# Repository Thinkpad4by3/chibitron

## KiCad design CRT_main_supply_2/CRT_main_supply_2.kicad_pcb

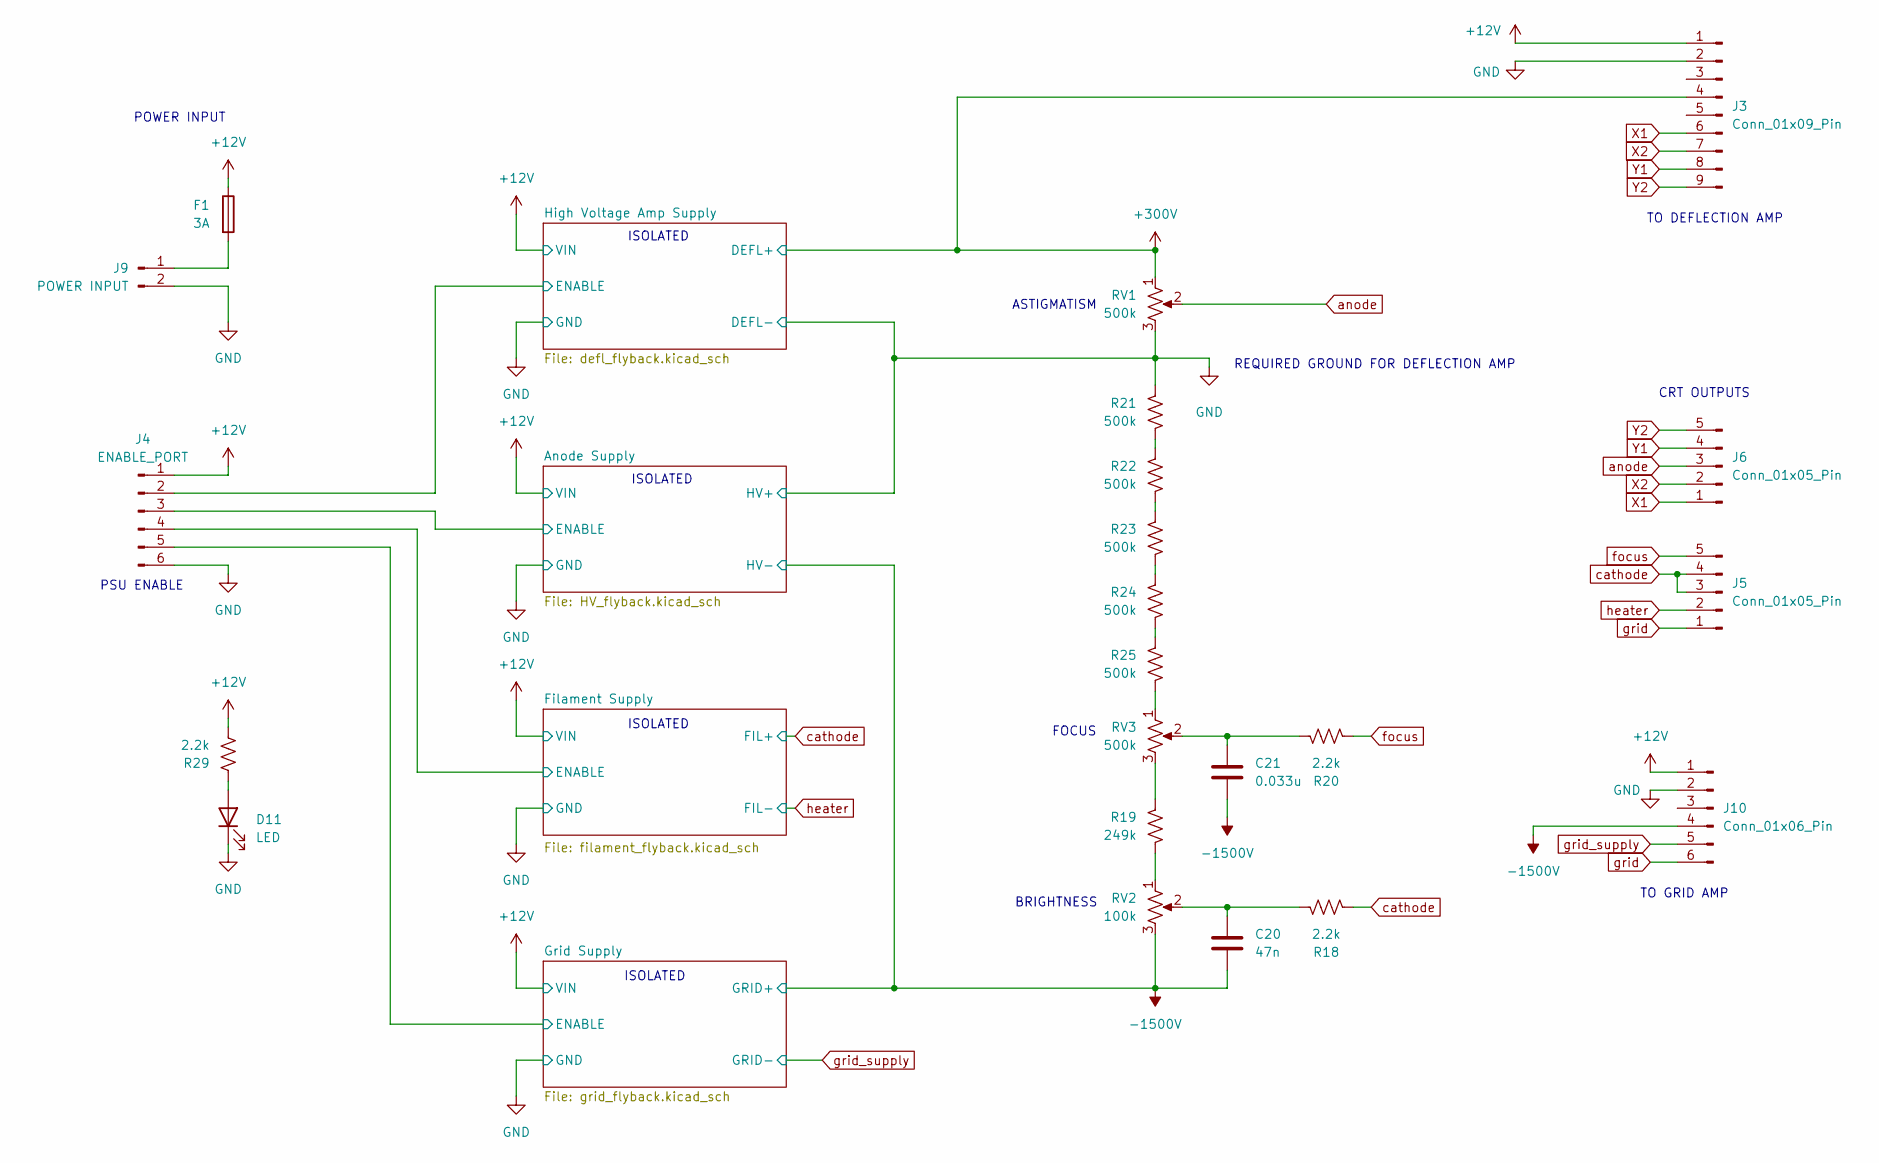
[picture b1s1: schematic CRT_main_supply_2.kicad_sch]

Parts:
C20: 47n; C_0805_2012Metric
C21: 0.033u; C_2225_5664Metric
D11: LED; LED_0805_2012Metric
F1: 3A; Fuse_1206_3216Metric
J3: Conn_01x09_Pin; Molex_KK-396_5273-09A_1x09_P3.96mm_Vertical
J4: ENABLE_PORT; Molex_KK-396_5273-06A_1x06_P3.96mm_Vertical
J5, J6: Conn_01x05_Pin; Molex_KK-396_5273-05A_1x05_P3.96mm_Vertical
J9: POWER INPUT; Molex_KK-396_5273-02A_1x02_P3.96mm_Vertical
J10: Conn_01x06_Pin; Molex_KK-396_5273-06A_1x06_P3.96mm_Vertical
R18, R20, R29: 2.2k; R_0805_2012Metric
R19: 249k; R_1206_3216Metric
R21, R22, R23, R24, R25: 500k; R_1206_3216Metric
RV1, RV3: 500k; Potentiometer_Bourns_3296W_Vertical
RV2: 100k; Potentiometer_Bourns_3296W_Vertical

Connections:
+12V: F1.1, J3.1, J4.1, J10.1, R29.2; also elsewhere on the board
+300V: J3.4, RV1.1; also elsewhere on the board
-1500V: C20.2, C21.2, J10.4, RV2.3; also elsewhere on the board
/Anode Supply/ENABLE: J4.3; also elsewhere on the board
/Filament Supply/ENABLE: J4.4; also elsewhere on the board
/Grid Supply/ENABLE: J4.5; also elsewhere on the board
/High Voltage Amp Supply/ENABLE: J4.2; also elsewhere on the board
GND: D11.1 (K), J3.2, J4.6, J9.2, J10.2, R21.1, RV1.3; also elsewhere on the board
unnamed: C20.1, R18.1, RV2.2
unnamed: C21.1, R20.1, RV3.2
unnamed: D11.2 (A), R29.1
unnamed: F1.2, J9.1
unnamed: R19.1, RV3.3
unnamed: R19.2, RV2.1
unnamed: R21.2, R22.1
unnamed: R22.2, R23.1
unnamed: R23.2, R24.1
unnamed: R24.2, R25.1
unnamed: R25.2, RV3.1
X1: J3.6, J6.1
X2: J3.7, J6.2
Y1: J3.8, J6.4
Y2: J3.9, J6.5
anode: J6.3, RV1.2
cathode: J5.3, J5.4, R18.2; also elsewhere on the board
focus: J5.5, R20.2
grid: J5.1, J10.6
grid_supply: J10.5; also elsewhere on the board
heater: J5.2; also elsewhere on the board

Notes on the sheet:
ISOLATED
TO GRID AMP
PSU ENABLE
POWER INPUT
REQUIRED GROUND FOR DEFLECTION AMP
CRT OUTPUTS
FOCUS
TO DEFLECTION AMP
BRIGHTNESS
ASTIGMATISM

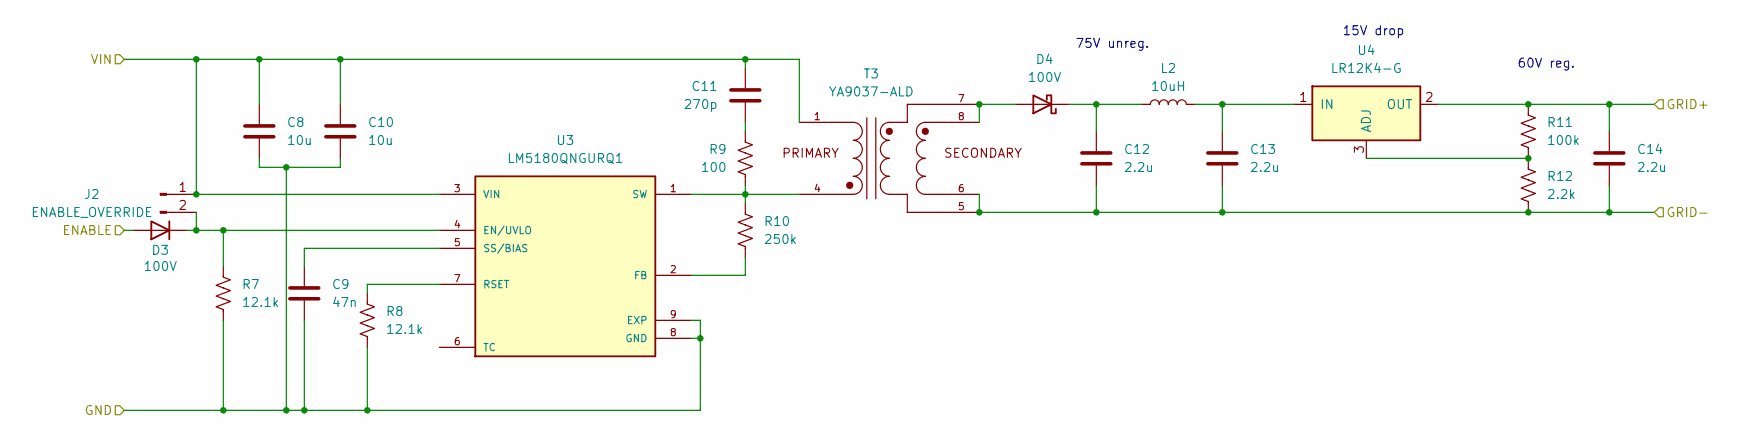
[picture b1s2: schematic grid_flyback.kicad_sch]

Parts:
C8, C10: 10u; C_0805_2012Metric
C9: 47n; C_0805_2012Metric
C11: 270p; C_0805_2012Metric
C12, C13, C14: 2.2u; C_1206_3216Metric
D3, D4: 100V; D_SOD-123F
J2: ENABLE_OVERRIDE; PinHeader_1x02_P2.54mm_Vertical
L2: 10uH; L_APV_ANR4018
R7, R8: 12.1k; R_0603_1608Metric
R9: 100; R_1206_3216Metric
R10: 250k; R_0805_2012Metric
R11: 100k; R_0805_2012Metric
R12: 2.2k; R_0805_2012Metric
T3: YA9037-ALD; XFMR_YA9033-ALD; PARTREV 05/12/21
U3: LM5180QNGURQ1; SON80P400X400X80-9N; PARTREV A
U4: LR12K4-G; TO-252-2

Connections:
+12V: C8.1, C10.1, C11.1, J2.1, T3.1, U3.3 (VIN); also elsewhere on the board
-1500V: C14.1, R11.1, U4.2 (OUT); also elsewhere on the board
/Grid Supply/ENABLE: D3.2 (A); also elsewhere on the board
GND: C8.2, C9.2, C10.2, R7.2, R8.2, U3.8 (GND), U3.9 (EXP); also elsewhere on the board
unnamed: C11.2, R9.1
unnamed: D3.1 (K), J2.2, R7.1, U3.4 (EN/UVLO)
unnamed: D4.2 (A), T3.7, T3.8
unnamed: C12.1, D4.1 (K), L2.1
unnamed: R10.2, U3.2 (FB)
unnamed: R8.1, U3.7 (RSET)
unnamed: C9.1, U3.5 (SS/BIAS)
unnamed: R9.2, R10.1, T3.4, U3.1 (SW)
unnamed: R11.2, R12.1, U4.3 (ADJ)
unnamed: C13.1, L2.2, U4.1 (IN)
grid_supply: C12.2, C13.2, C14.2, R12.2, T3.5, T3.6; also elsewhere on the board

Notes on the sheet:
15V drop
75V unreg.
60V reg.

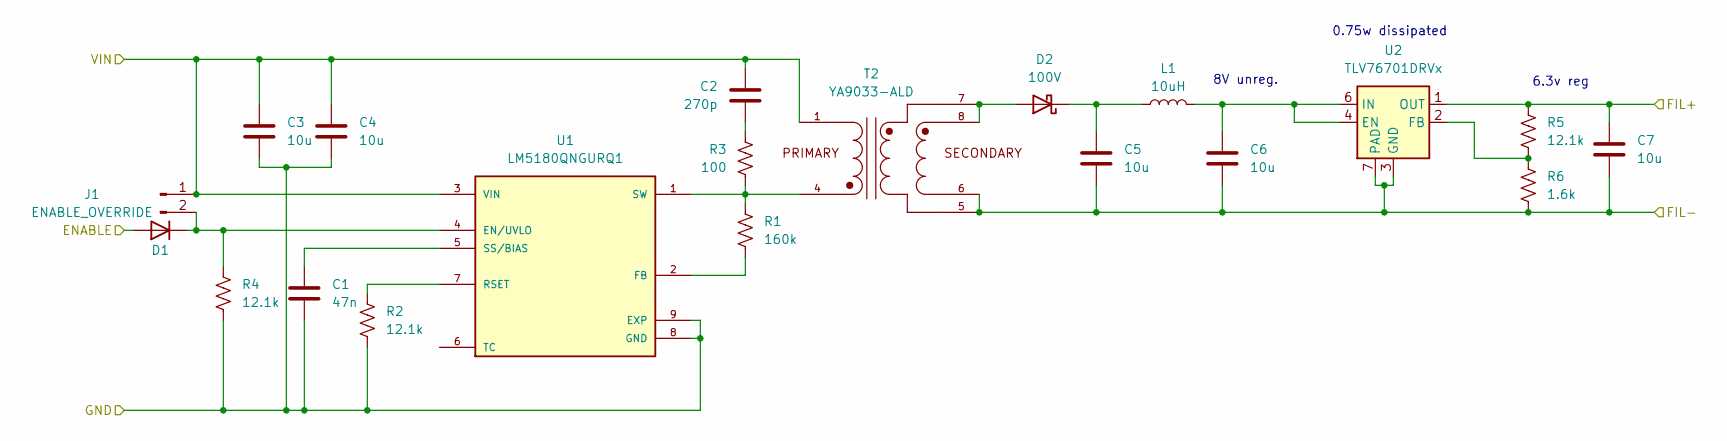
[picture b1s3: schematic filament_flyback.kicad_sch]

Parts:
C1: 47n; C_0805_2012Metric
C2: 270p; C_0805_2012Metric
C3, C4, C5, C6, C7: 10u; C_0805_2012Metric
D1, D2: 100V; D_SOD-123F
J1: ENABLE_OVERRIDE; PinHeader_1x02_P2.54mm_Vertical
L1: 10uH; L_APV_ANR4018
R1: 160k; R_0805_2012Metric
R2, R4, R5: 12.1k; R_0603_1608Metric
R3: 100; R_1206_3216Metric
R6: 1.6k; R_0805_2012Metric
T2: YA9033-ALD; XFMR_YA9033-ALD; PARTREV 05/12/21
U1: LM5180QNGURQ1; SON80P400X400X80-9N; PARTREV A
U2: TLV76701DRVx; WSON-6-1EP_2x2mm_P0.65mm_EP1x1.6mm_ThermalVias

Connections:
+12V: C2.1, C3.1, C4.1, J1.1, T2.1, U1.3 (VIN); also elsewhere on the board
/Filament Supply/ENABLE: D1.2 (A); also elsewhere on the board
GND: C1.2, C3.2, C4.2, R2.2, R4.2, U1.8 (GND), U1.9 (EXP); also elsewhere on the board
unnamed: C2.2, R3.1
unnamed: D1.1 (K), J1.2, R4.1, U1.4 (EN/UVLO)
unnamed: D2.2 (A), T2.7, T2.8
unnamed: C5.1, D2.1 (K), L1.1
unnamed: R1.2, U1.2 (FB)
unnamed: R2.1, U1.7 (RSET)
unnamed: C1.1, U1.5 (SS/BIAS)
unnamed: R1.1, R3.2, T2.4, U1.1 (SW)
unnamed: C6.1, L1.2, U2.4 (EN), U2.6 (IN)
unnamed: R5.2, R6.1, U2.2 (FB)
cathode: C7.1, R5.1, U2.1 (OUT); also elsewhere on the board
heater: C5.2, C6.2, C7.2, R6.2, T2.5, T2.6, U2.3 (GND), U2.5 (GND), U2.7 (PAD); also elsewhere on the board

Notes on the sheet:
6.3v reg
0.75w dissipated
8V unreg.

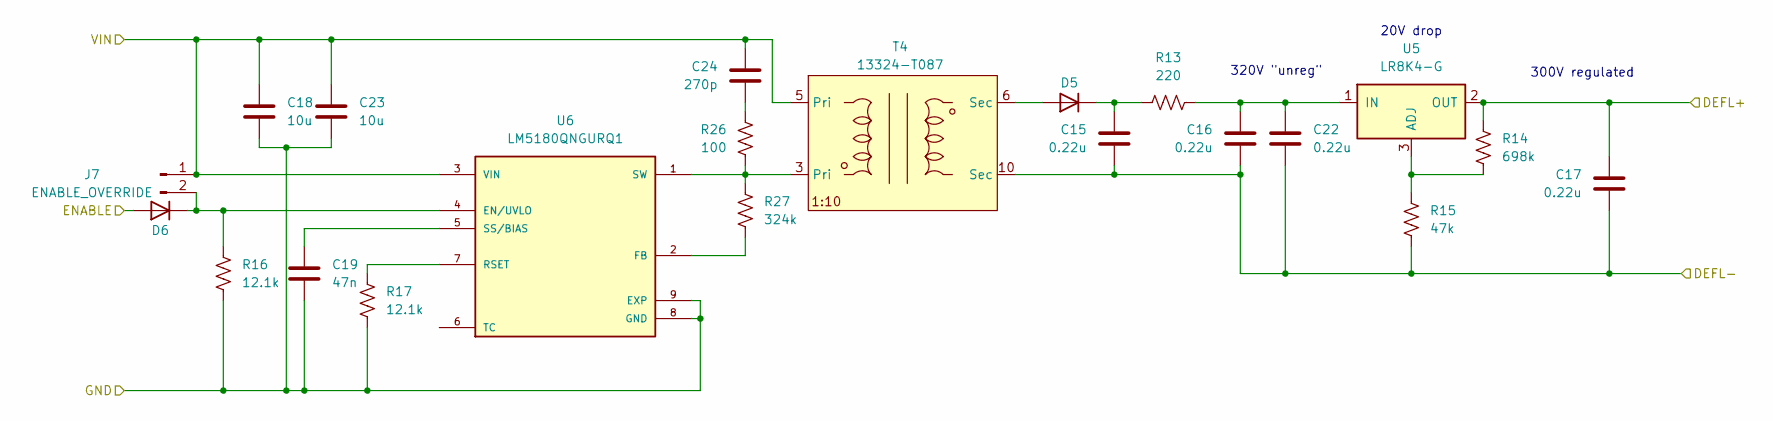
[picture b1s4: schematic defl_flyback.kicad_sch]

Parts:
C15, C16, C17, C22: 0.22u; C_1812_4532Metric
C18, C23: 10u; C_0805_2012Metric
C19: 47n; C_0805_2012Metric
C24: 270p; C_0805_2012Metric
D5: 800V; D_SOD-123F
D6: 100V; D_SOD-123F
J7: ENABLE_OVERRIDE; PinHeader_1x02_P2.54mm_Vertical
R13: 220; R_1206_3216Metric
R14: 698k; R_0805_2012Metric
R15: 47k; R_0805_2012Metric
R16, R17: 12.1k; R_0603_1608Metric
R26: 100; R_1206_3216Metric
R27: 324k; R_0805_2012Metric
T4: 13324-T087
U5: LR8K4-G; TO-252-2
U6: LM5180QNGURQ1; SON80P400X400X80-9N; PARTREV A

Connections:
+12V: C18.1, C23.1, C24.1, J7.1, T4.5 (Pri), U6.3 (VIN); also elsewhere on the board
+300V: C17.2, R14.1, U5.2 (OUT); also elsewhere on the board
/High Voltage Amp Supply/ENABLE: D6.2 (A); also elsewhere on the board
GND: C15.2, C16.1, C17.1, C18.2, C19.2, C22.1, C23.2, R15.2, R16.2, R17.2, T4.10 (Sec), U6.8 (GND), U6.9 (EXP); also elsewhere on the board
unnamed: C24.2, R26.1
unnamed: D5.2 (A), T4.6 (Sec)
unnamed: C15.1, D5.1 (K), R13.1
unnamed: D6.1 (K), J7.2, R16.1, U6.4 (EN/UVLO)
unnamed: R14.2, R15.1, U5.3 (ADJ)
unnamed: C16.2, C22.2, R13.2, U5.1 (IN)
unnamed: R27.2, U6.2 (FB)
unnamed: R17.1, U6.7 (RSET)
unnamed: C19.1, U6.5 (SS/BIAS)
unnamed: R26.2, R27.1, T4.3 (Pri), U6.1 (SW)

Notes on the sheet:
320V "unreg"
20V drop
300V regulated

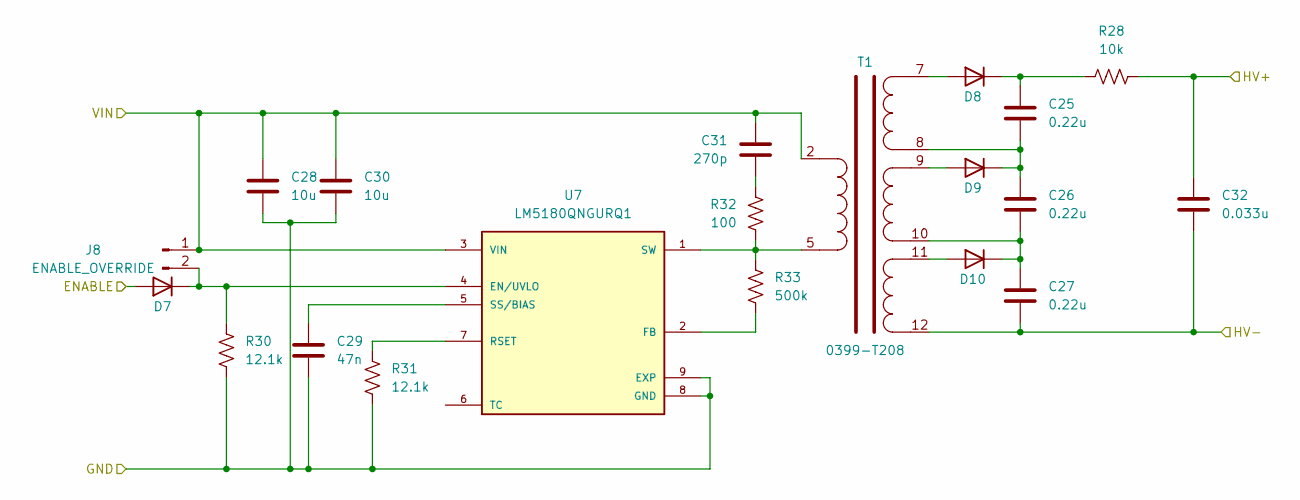
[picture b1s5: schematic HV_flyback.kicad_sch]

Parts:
C25, C26, C27: 0.22u; C_1812_4532Metric
C28, C30: 10u; C_0805_2012Metric
C29: 47n; C_0805_2012Metric
C31: 270p; C_0805_2012Metric
C32: 0.033u; C_2225_5664Metric
D7: 100V; D_SOD-123F
D8, D9, D10: 800V; D_SOD-123F
J8: ENABLE_OVERRIDE; PinHeader_1x02_P2.54mm_Vertical
R28: 10k; R_1206_3216Metric
R30, R31: 12.1k; R_0603_1608Metric
R32: 100; R_1206_3216Metric
R33: 500k; R_1206_3216Metric
T1: 0399-T208
U7: LM5180QNGURQ1; SON80P400X400X80-9N; PARTREV A

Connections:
+12V: C28.1, C30.1, C31.1, J8.1, T1.2, U7.3 (VIN); also elsewhere on the board
-1500V: C27.2, C32.2, T1.12; also elsewhere on the board
/Anode Supply/ENABLE: D7.2 (A); also elsewhere on the board
GND: C28.2, C29.2, C30.2, C32.1, R28.2, R30.2, R31.2, U7.8 (GND), U7.9 (EXP); also elsewhere on the board
unnamed: C31.2, R32.1
unnamed: D7.1 (K), J8.2, R30.1, U7.4 (EN/UVLO)
unnamed: D8.2 (A), T1.7
unnamed: C25.1, D8.1 (K), R28.1
unnamed: D9.2 (A), T1.9
unnamed: C25.2, C26.1, D9.1 (K), T1.8
unnamed: D10.2 (A), T1.11
unnamed: C26.2, C27.1, D10.1 (K), T1.10
unnamed: R33.2, U7.2 (FB)
unnamed: R31.1, U7.7 (RSET)
unnamed: C29.1, U7.5 (SS/BIAS)
unnamed: R32.2, R33.1, T1.5, U7.1 (SW)

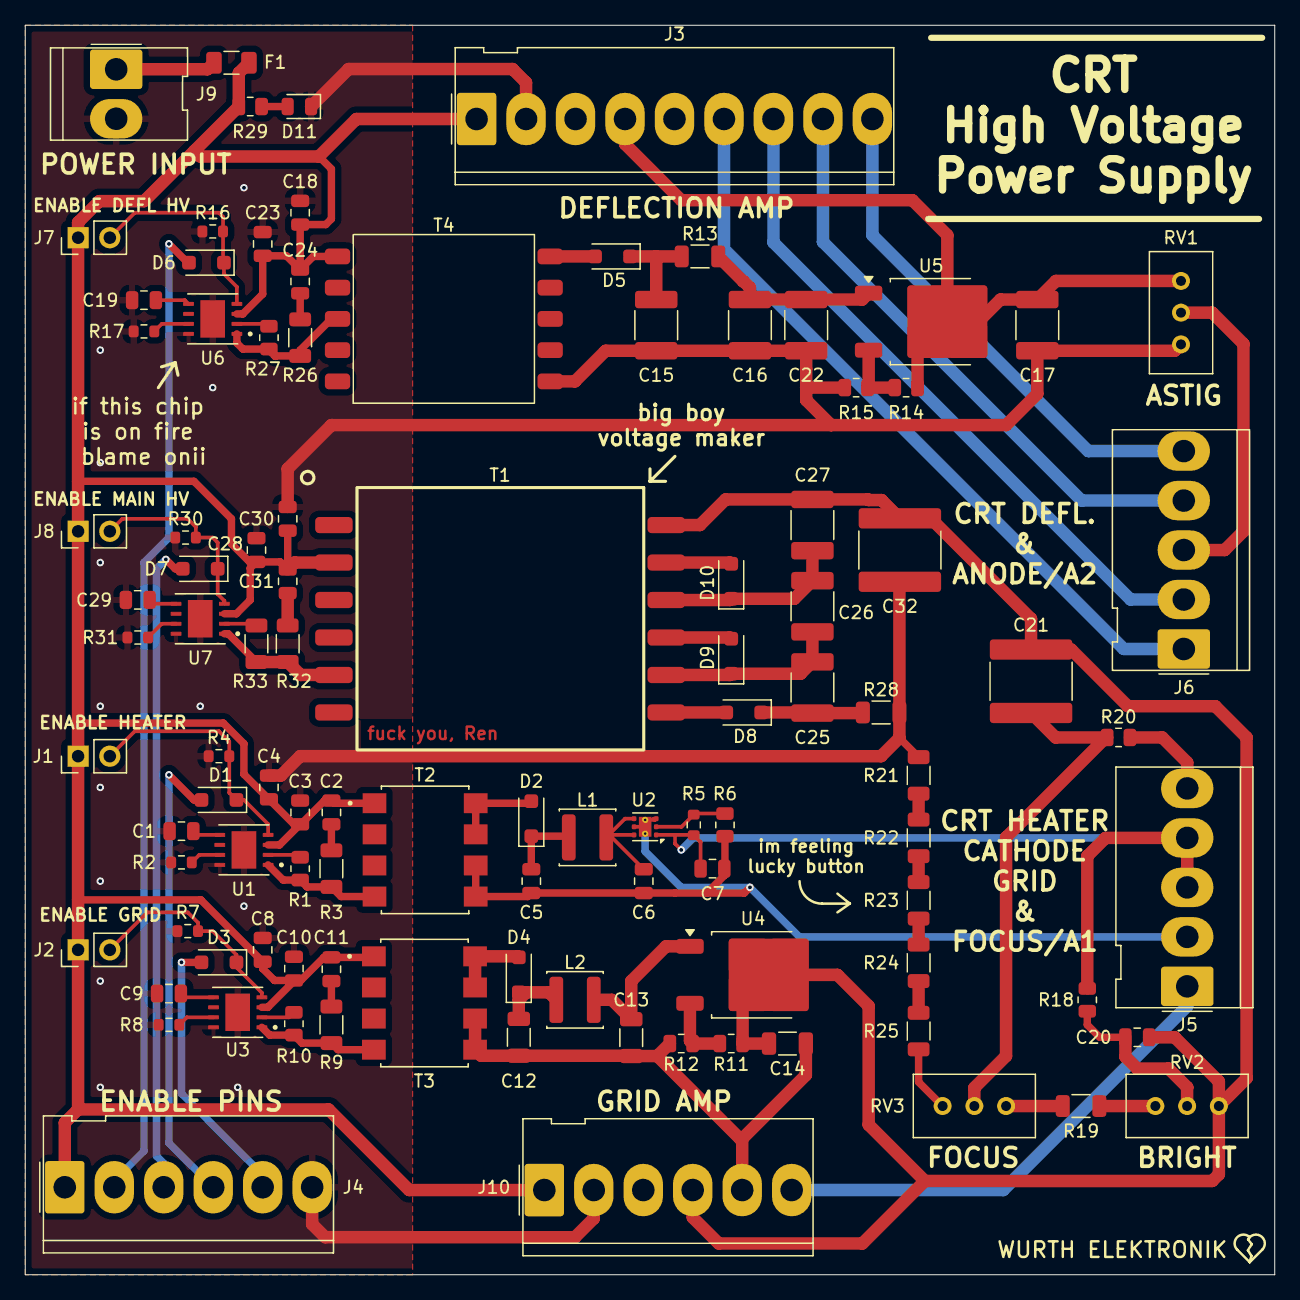
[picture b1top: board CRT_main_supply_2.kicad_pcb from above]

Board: 2 copper layers, 100.0 x 100.0 mm, 103 parts (0 on the bottom side), 71 nets.
